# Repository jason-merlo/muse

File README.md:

# Muse
A Spark Core based music visualizer using the MSEGEQ7 spectrum analyzer IC

Bill of materials for v1.2 located at: https://docs.google.com/spreadsheets/d/1B2xJy5_H-dvUnllyMT6rd3qgGW_fhY_ttB6ZkNy4PM8/

A full writeup for this project will hopefully come sometime in the near future.

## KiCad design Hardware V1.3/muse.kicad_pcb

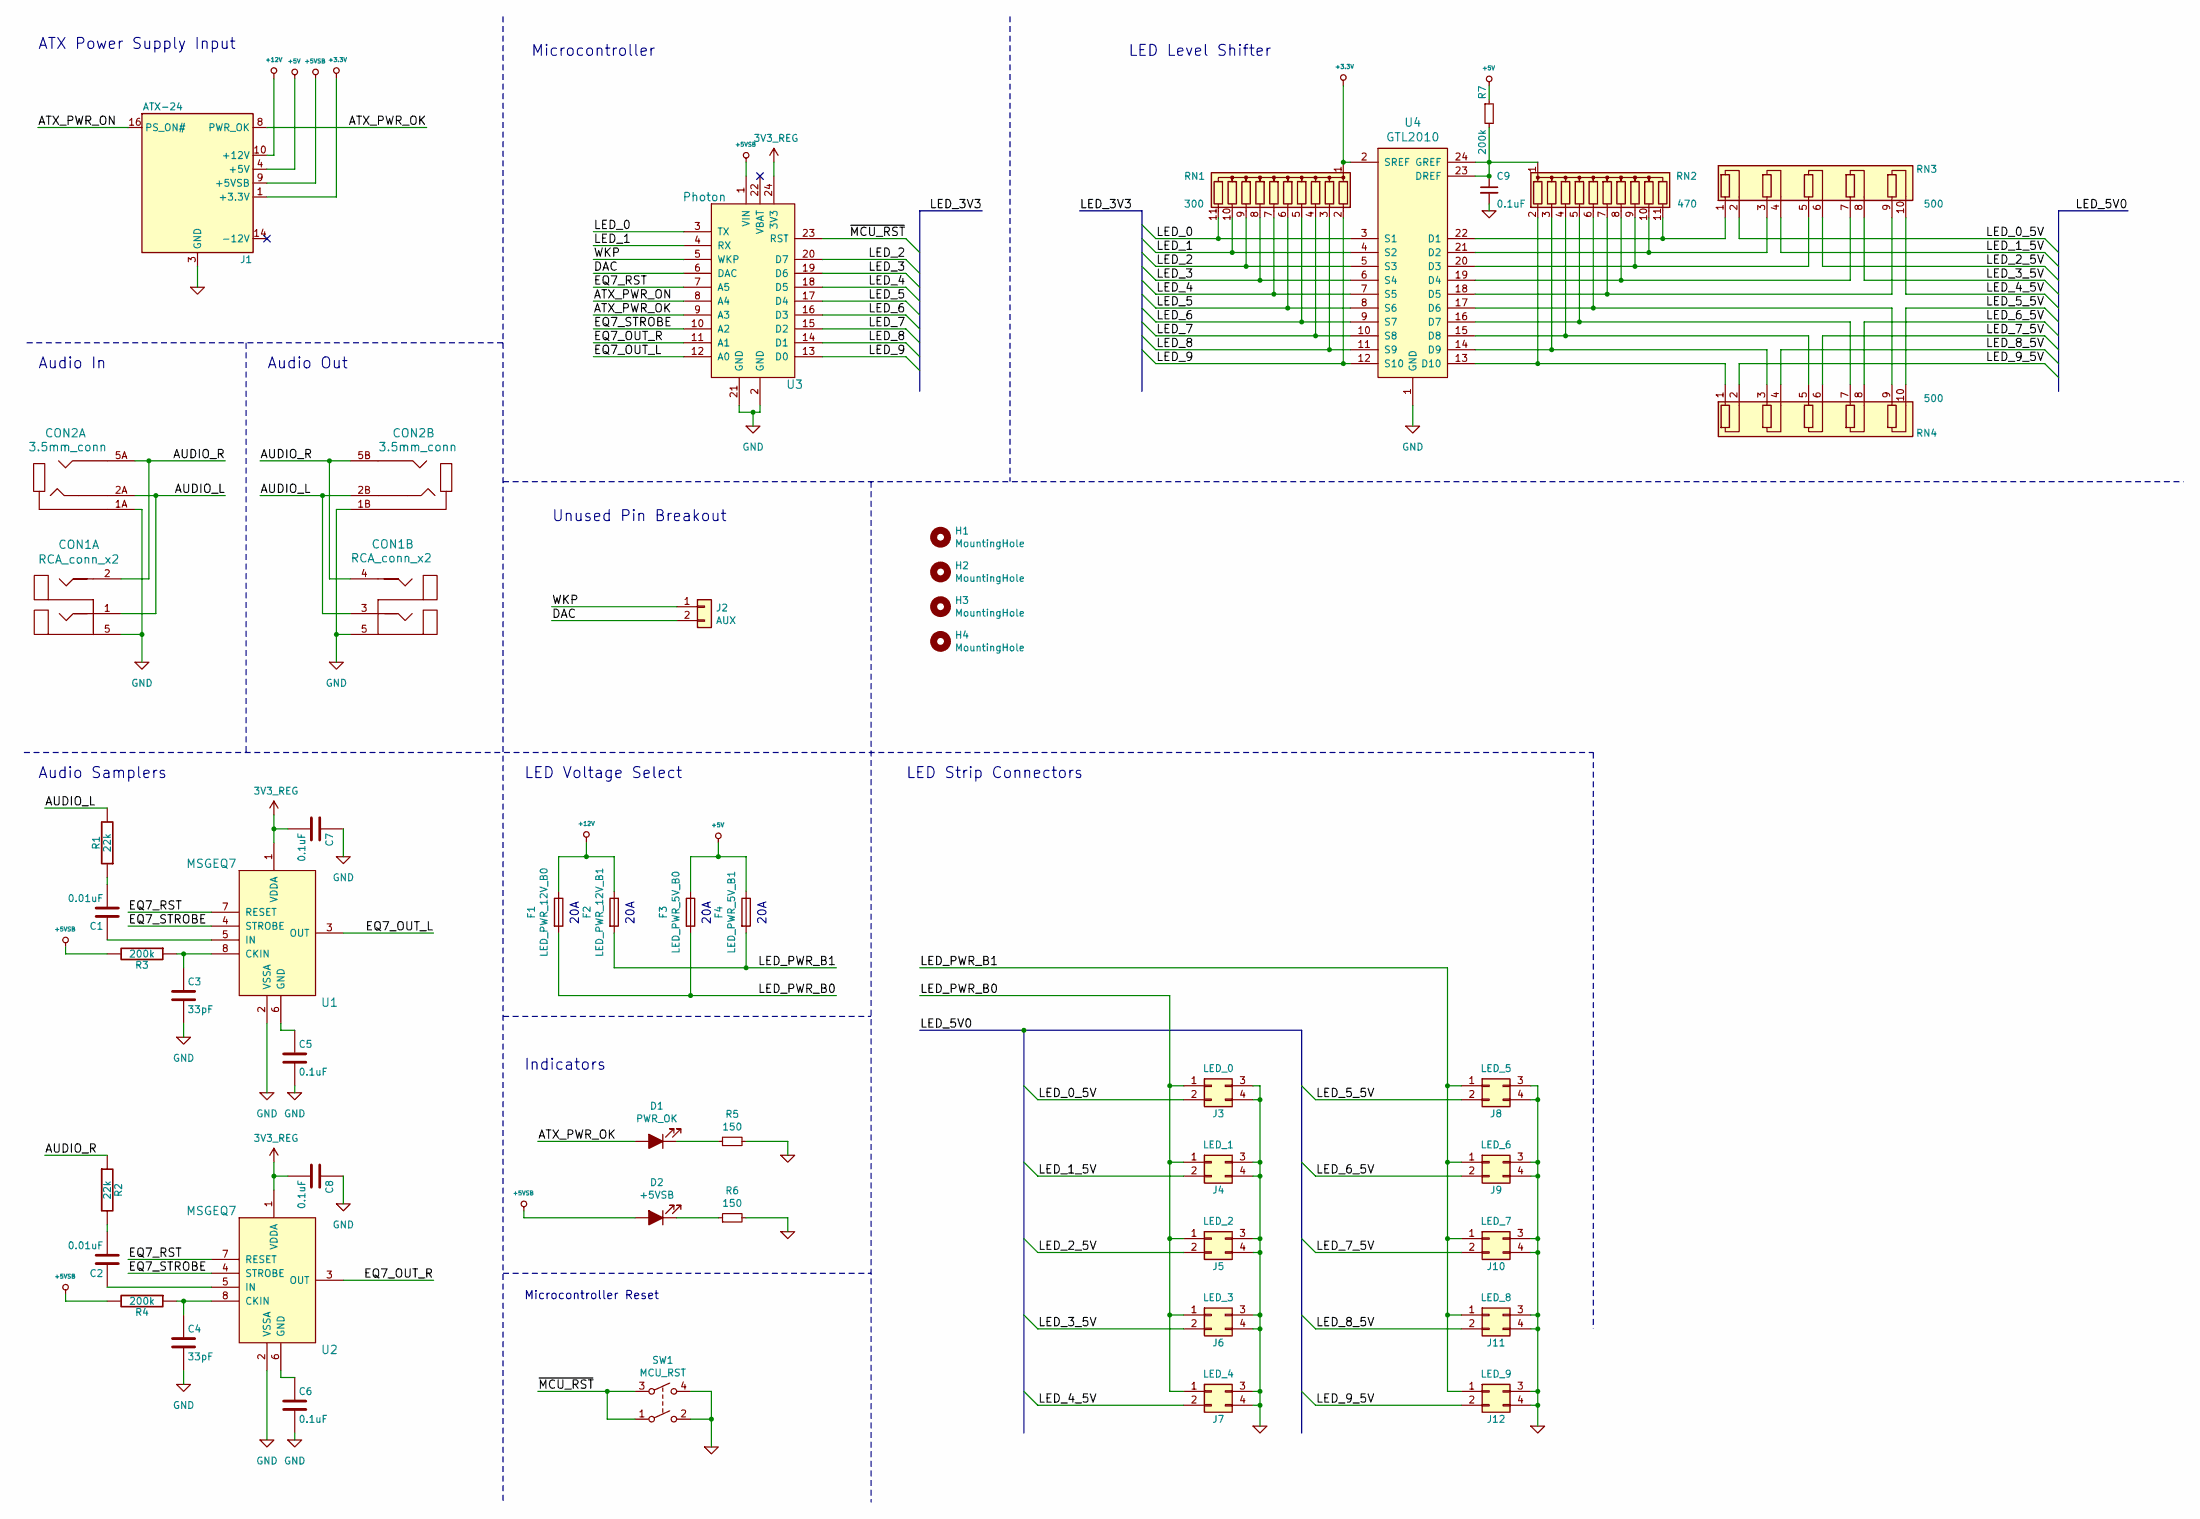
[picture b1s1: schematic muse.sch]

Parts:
C1, C2: 0.01uF; C_Rect_L4.6mm_W3.0mm_P2.50mm_MKS02_FKP02
C3, C4: 33pF; C_Rect_L4.6mm_W3.0mm_P2.50mm_MKS02_FKP02
C5, C6, C7, C8, C9: 0.1uF; C_Rect_L4.6mm_W3.0mm_P2.50mm_MKS02_FKP02
CON1: RCA_conn_x2; PJRAS2X2S01X
CON2: 3.5mm_conn; STX423535N
D1: PWR_OK; LED_D3.0mm
D2: +5VSB; LED_D3.0mm
F1: LED_PWR_12V_B0; Fuseholder_Blade_Mini_Keystone_3568
F2: LED_PWR_12V_B1; Fuseholder_Blade_Mini_Keystone_3568
F3: LED_PWR_5V_B0; Fuseholder_Blade_Mini_Keystone_3568
F4: LED_PWR_5V_B1; Fuseholder_Blade_Mini_Keystone_3568
H1, H2, H3, H4: MountingHole; MountingHole_3.2mm_M3
J1: ATX-24; Molex_Mini-Fit_Jr_5569-24A1_2x12_P4.20mm_Horizontal
J2: AUX; PinHeader_1x02_P2.54mm_Vertical
J3: LED_0; Molex_Mini-Fit_Jr_5569-04A1_2x02_P4.20mm_Horizontal
J4: LED_1; Molex_Mini-Fit_Jr_5569-04A1_2x02_P4.20mm_Horizontal
J5: LED_2; Molex_Mini-Fit_Jr_5569-04A1_2x02_P4.20mm_Horizontal
J6: LED_3; Molex_Mini-Fit_Jr_5569-04A1_2x02_P4.20mm_Horizontal
J7: LED_4; Molex_Mini-Fit_Jr_5569-04A1_2x02_P4.20mm_Horizontal
J8: LED_5; Molex_Mini-Fit_Jr_5569-04A1_2x02_P4.20mm_Horizontal
J9: LED_6; Molex_Mini-Fit_Jr_5569-04A1_2x02_P4.20mm_Horizontal
J10: LED_7; Molex_Mini-Fit_Jr_5569-04A1_2x02_P4.20mm_Horizontal
J11: LED_8; Molex_Mini-Fit_Jr_5569-04A1_2x02_P4.20mm_Horizontal
J12: LED_9; Molex_Mini-Fit_Jr_5569-04A1_2x02_P4.20mm_Horizontal
R1, R2: 22k; R_Axial_DIN0207_L6.3mm_D2.5mm_P10.16mm_Horizontal
R3, R4, R7: 200k; R_Axial_DIN0207_L6.3mm_D2.5mm_P10.16mm_Horizontal
R5, R6: 150; R_Axial_DIN0207_L6.3mm_D2.5mm_P10.16mm_Horizontal
RN1: 300; R_Array_SIP11
RN2: 470; R_Array_SIP11
RN3, RN4: 500; R_Array_SIP10
SW1: MCU_RST; SW_TH_Tactile_Omron_B3F-10xx
U1, U2: MSGEQ7; DIP-8_W7.62mm_LongPads
U3: Photon; photon_tht
U4: GTL2010; TSSOP-24_4.4x7.8mm_P0.65mm

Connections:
+3.3V: J1.1 (+3.3V), J1.2 (+3.3V), J1.12 (+3.3V), J1.13 (+3.3V), RN1.1 (common), U4.2 (SREF)
+3.3V_REG: C7.2, C8.2, U1.1 (VDDA), U2.1 (VDDA), U3.24 (3V3)
+5V: F3.1, F4.1, J1.4 (+5V), J1.6 (+5V), J1.21 (+5V), J1.22 (+5V), J1.23 (+5V), R7.1
+5VSB: D2.2 (A), J1.9 (+5VSB), R3.2, R4.2, U3.1 (VIN)
+12V: F1.1, F2.1, J1.10 (+12V), J1.11 (+12V)
/ATX_PWR_OK: D1.2 (A), J1.8 (PWR_OK), U3.9 (A3)
/ATX_PWR_ON: J1.16 (PS_ON#), U3.8 (A4)
/AUDIO_L: CON1.1, CON1.3, CON2.2A, CON2.2B, R1.2
/AUDIO_R: CON1.2, CON1.4, CON2.5A, CON2.5B, R2.1
/DAC: J2.2, U3.6 (DAC)
/EQ7_OUT_L: U1.3 (OUT), U3.12 (A0)
/EQ7_OUT_R: U2.3 (OUT), U3.11 (A1)
/EQ7_RST: U1.7 (RESET), U2.7 (RESET), U3.7 (A5)
/EQ7_STROBE: U1.4 (STROBE), U2.4 (STROBE), U3.10 (A2)
/LED_0: RN1.11 (R10), U3.3 (TX), U4.3 (S1)
/LED_0_5V: J3.2, RN3.2 (R1.2)
/LED_1: RN1.10 (R9), U3.4 (RX), U4.4 (S2)
/LED_1_5V: J4.2, RN3.4 (R2.2)
/LED_2: RN1.9 (R8), U3.20 (D7), U4.5 (S3)
/LED_2_5V: J5.2, RN3.6 (R3.2)
/LED_3: RN1.8 (R7), U3.19 (D6), U4.6 (S4)
/LED_3_5V: J6.2, RN3.8 (R4.2)
/LED_4: RN1.7 (R6), U3.18 (D5), U4.7 (S5)
/LED_4_5V: J7.2, RN3.10 (R5.2)
/LED_5: RN1.6 (R5), U3.17 (D4), U4.8 (S6)
/LED_5_5V: J8.2, RN4.10 (R5.2)
/LED_6: RN1.5 (R4), U3.16 (D3), U4.9 (S7)
/LED_6_5V: J9.2, RN4.8 (R4.2)
/LED_7: RN1.4 (R3), U3.15 (D2), U4.10 (S8)
/LED_7_5V: J10.2, RN4.6 (R3.2)
/LED_8: RN1.3 (R2), U3.14 (D1), U4.11 (S9)
/LED_8_5V: J11.2, RN4.4 (R2.2)
/LED_9: RN1.2 (R1), U3.13 (D0), U4.12 (S10)
/LED_9_5V: J12.2, RN4.2 (R1.2)
/LED_PWR_B0: F1.2, F3.2, J3.1, J4.1, J5.1, J6.1, J7.1
/LED_PWR_B1: F2.2, F4.2, J8.1, J9.1, J10.1, J11.1, J12.1
/WKP: J2.1, U3.5 (WKP)
/~MCU_RST: SW1.1, SW1.3, U3.23 (RST)
unnamed: C1.1, U1.5 (IN)
unnamed: C1.2, R1.1
unnamed: C2.1, U2.5 (IN)
unnamed: C2.2, R2.2
unnamed: C3.1, R3.1, U1.8 (CKIN)
unnamed: C4.1, R4.1, U2.8 (CKIN)
unnamed: C5.1, U1.6 (GND)
unnamed: C6.1, U2.6 (GND)
unnamed: C9.1, R7.2, RN2.1 (common), U4.23 (DREF), U4.24 (GREF)
unnamed: D1.1 (K), R5.1
unnamed: D2.1 (K), R6.1
unnamed: RN2.2 (R1), RN4.1 (R1.1), U4.13 (D10)
unnamed: RN2.3 (R2), RN4.3 (R2.1), U4.14 (D9)
unnamed: RN2.4 (R3), RN4.5 (R3.1), U4.15 (D8)
unnamed: RN2.5 (R4), RN4.7 (R4.1), U4.16 (D7)
unnamed: RN2.6 (R5), RN4.9 (R5.1), U4.17 (D6)
unnamed: RN2.7 (R6), RN3.9 (R5.1), U4.18 (D5)
unnamed: RN2.8 (R7), RN3.7 (R4.1), U4.19 (D4)
unnamed: RN2.9 (R8), RN3.5 (R3.1), U4.20 (D3)
unnamed: RN2.10 (R9), RN3.3 (R2.1), U4.21 (D2)
unnamed: RN2.11 (R10), RN3.1 (R1.1), U4.22 (D1)

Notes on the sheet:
Audio Samplers
LED Level Shifter
ATX Power Supply Input
Audio Out
Audio In
Microcontroller
LED Strip Connectors
Unused Pin Breakout
20A
LED Voltage Select
Indicators
Microcontroller Reset

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
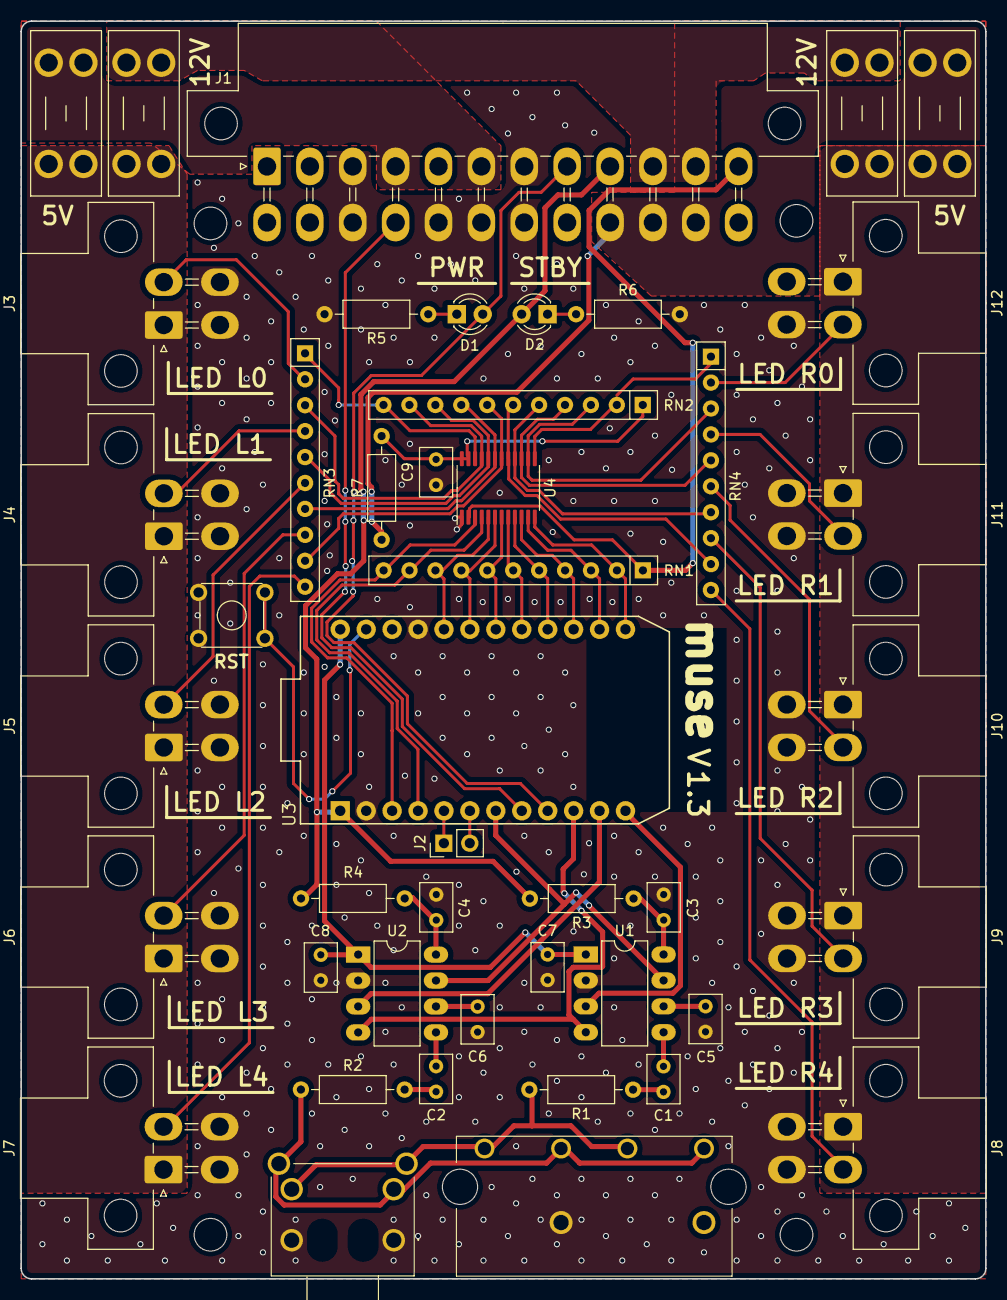
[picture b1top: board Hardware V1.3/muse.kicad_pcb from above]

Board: 2 copper layers, 94.5 x 123.2 mm, 49 parts (0 on the bottom side), 60 nets.

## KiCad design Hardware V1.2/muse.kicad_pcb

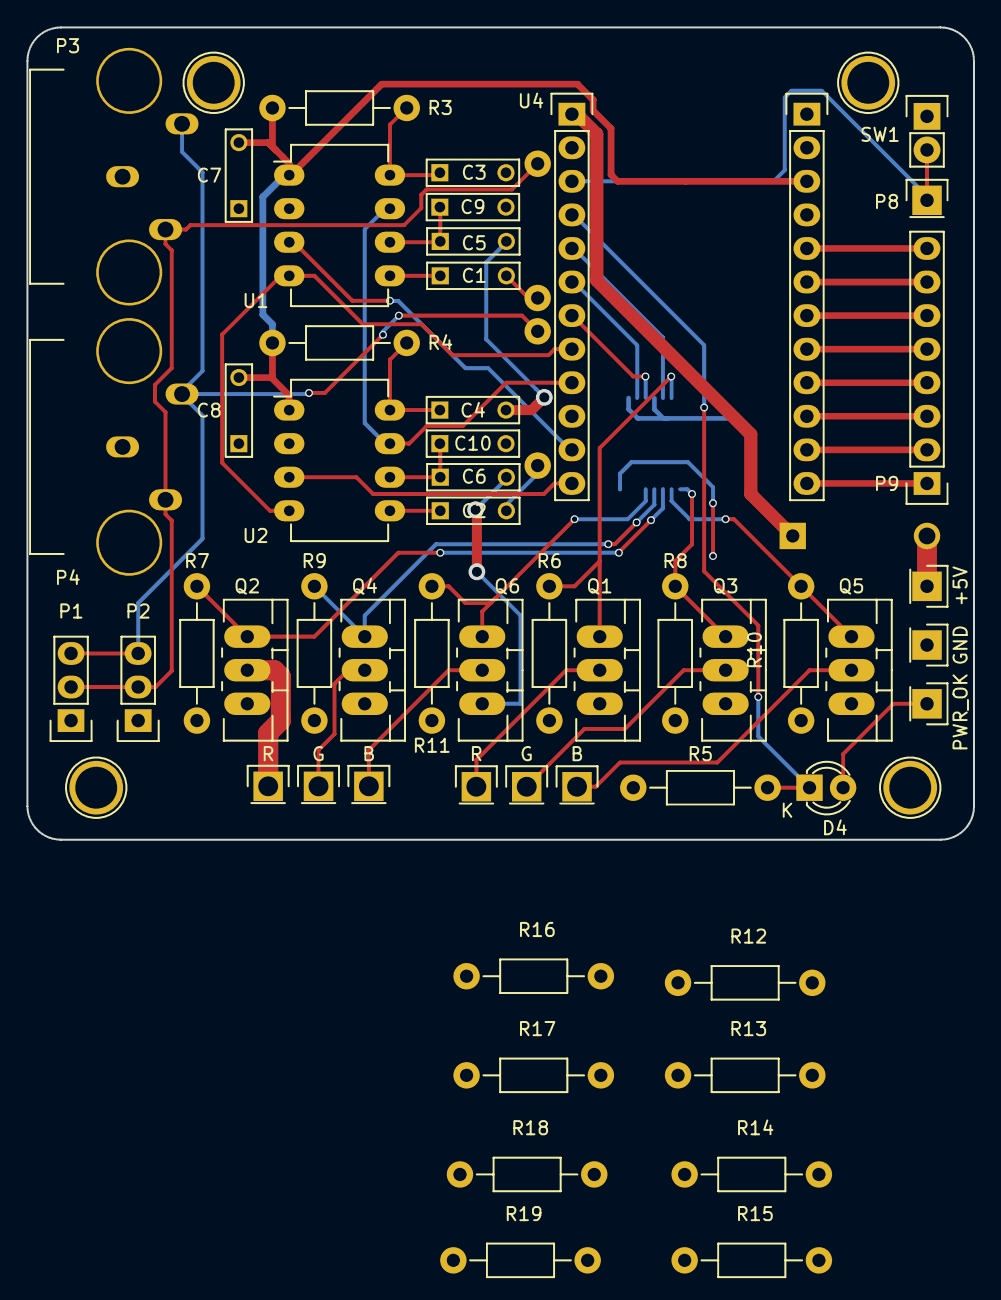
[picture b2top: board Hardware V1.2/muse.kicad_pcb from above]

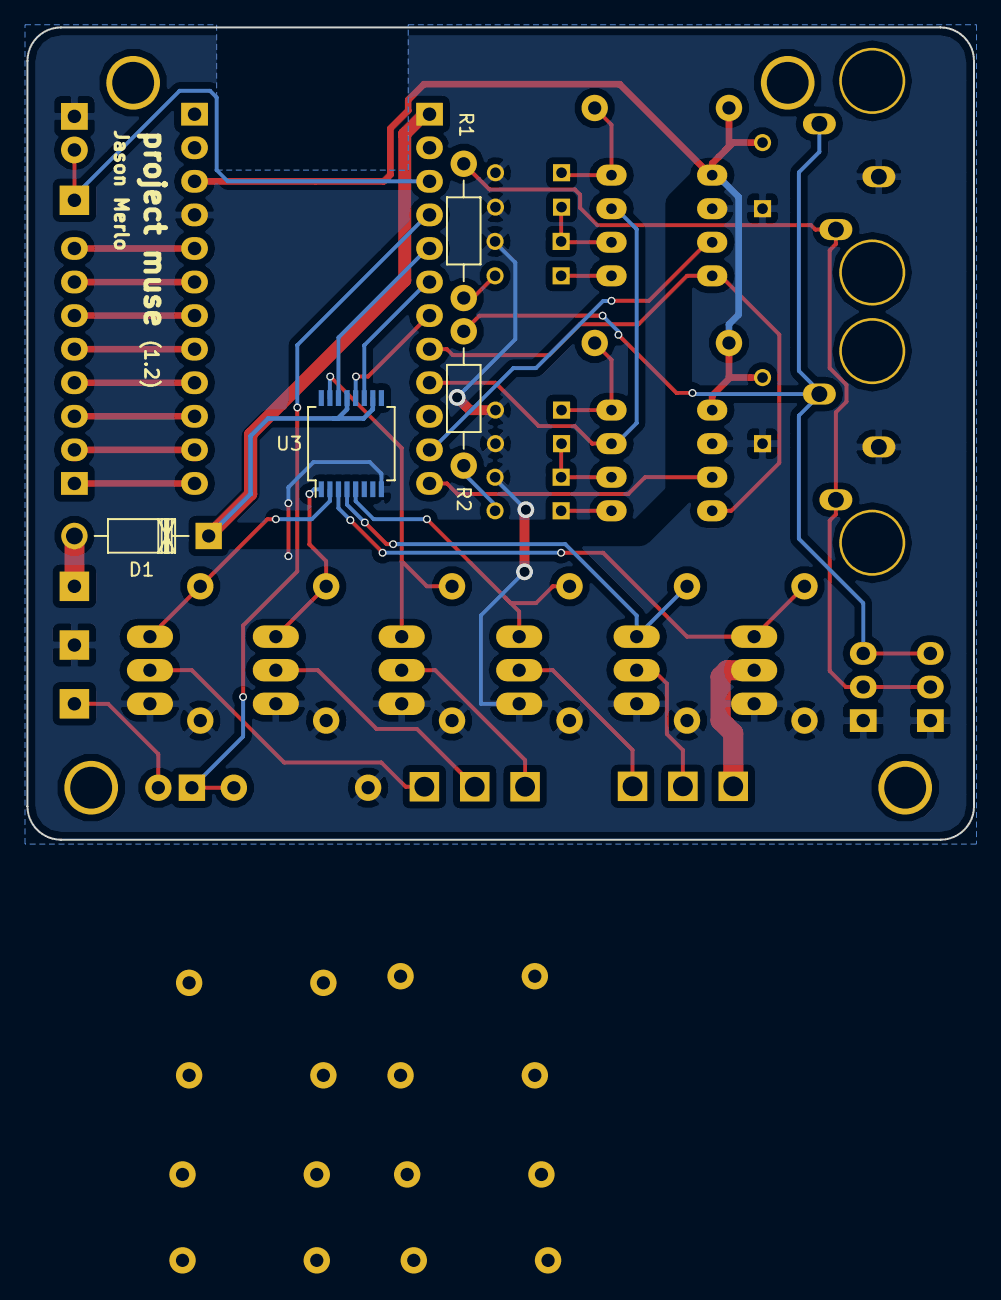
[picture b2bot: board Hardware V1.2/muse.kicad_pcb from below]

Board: 2 copper layers, 71.6 x 61.5 mm, 57 parts (4 on the bottom side), 50 nets.

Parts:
+5V: ATX_PWR; Pin_Header_Straight_1x01
B: LED_B; Pin_Header_Straight_1x01
B#2: LED_B; Pin_Header_Straight_1x01
C1, C2: 0.01uF; C_Rect_L7_W2_P5
C3, C4: 33pF; C_Rect_L7_W2_P5
C5, C6, C7, C8: 0.1uF; C_Rect_L7_W2_P5
C9, C10: 10uF; C_Rect_L7_W2_P5
D1: LED_R; Diode_DO-41_SOD81_Horizontal_RM10
D4: PWR_LED; LED-3MM
G: LED_G; Pin_Header_Straight_1x01
G#2: LED_G; Pin_Header_Straight_1x01
GND: ATX_GND; Pin_Header_Straight_1x01
P1, P2: 3.5mm_line; Pin_Header_Straight_1x03
P3, P4: RCA; Audio_RCA_Vertical
P8: ATX_PS_ON; Pin_Header_Straight_1x01
P9: LED_Signal; Pin_Header_Straight_1x08
PWR_OK: ATX_PWR_OK; Pin_Header_Straight_1x01
Q1, Q2, Q3, Q4, Q5, Q6: FQP30N06L; TO-220_Neutral123_Vertical_LargePads
R: LED_R; Pin_Header_Straight_1x01
R1, R2: 22k; Resistor_Horizontal_RM10mm
R3, R4: 200k; Resistor_Horizontal_RM10mm
R5, R12, R13, R14, R15, R16, R17, R18, R19: 470; Resistor_Horizontal_RM10mm
R6, R7, R8, R9, R10, R11: 10k; Resistor_Horizontal_RM10mm
R#2: LED_R; Pin_Header_Straight_1x01
SW1: PWR_SW; Pin_Header_Straight_1x02
U1, U2: MSGEQ7; DIP-8_W7.62mm_LongPads
U3: 74LS595; SSOP-16_5.3x6.2mm_Pitch0.65mm
U4: Spark_Core

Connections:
+3.3V: C7.2, C8.2, R3.2, R4.2, U1.1, U2.1, U4.22
+5V: U3.10, U3.13, U4.1
/ATX_PWR_OK: D4.1, U4.4
/ATX_PWR_ON: P8.1, U4.3
/Aout_L: U1.3, U4.11
/Aout_R: U2.3, U4.12
/LED_0: R12.2, U4.13
/LED_0_B: Q5.1, R10.2, U3.2
/LED_0_G: Q3.1, R8.2, U3.1
/LED_0_R: Q1.1, R6.2, U3.15
/LED_1: R13.2, U4.14
/LED_1_B: Q6.1, R11.2, U3.5
/LED_1_G: Q4.1, R9.2, U3.4
/LED_1_R: Q2.1, R7.2, U3.3
/LED_2: R14.2, U4.15
/LED_3: R15.2, U4.16
/LED_4: R16.2, U4.17
/LED_5: R17.2, U4.18
/LED_6: R18.2, U4.19
/LED_7: R19.2, U4.20
/RGB_CLK: U3.11, U4.6
/RGB_DAT: U3.14, U4.5
/RGB_LAT: U3.12, U4.7
/RST: U1.7, U2.7, U4.9
/STROBE: U1.4, U2.4, U4.8
/audio_l: P1.2, P2.2, P3.2, P4.2, R1.2
/audio_r: P1.3, P2.3, P3.3, P4.3, R2.1
GND: C3.2, C4.2, C5.2, C6.2, C7.1, C8.1, C9.2, C10.2, GND.1, P1.1, P2.1, P3.1, P4.1, Q1.3, Q2.3, Q3.3, Q4.3, Q5.3, Q6.3, R5.1, R6.1, R7.1, R8.1, R9.1, R10.1, R11.1, SW1.1, U1.2, U2.2, U3.8, U4.2, U4.21
unnamed: C1.1, U1.5
unnamed: C1.2, R1.1
unnamed: C2.1, U2.5
unnamed: C2.2, R2.2
unnamed: C3.1, R3.1, U1.8
unnamed: C4.1, R4.1, U2.8
unnamed: C5.1, C9.1, U1.6
unnamed: C6.1, C10.1, U2.6
unnamed: D1.1, Q1.2
unnamed: Q5.2, R#2.1
unnamed: D4.2, R5.2
unnamed: G.1, Q2.2
unnamed: G#2.1, Q4.2
unnamed: B.1, Q6.2
unnamed: P9.1, R12.1
unnamed: P9.2, R13.1
unnamed: P9.3, R14.1
unnamed: P9.4, R15.1
unnamed: P9.5, R16.1
unnamed: P9.6, R17.1
unnamed: P9.7, R18.1
unnamed: P9.8, R19.1

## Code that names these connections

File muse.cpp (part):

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#if EXTENDED_LAYOUT
// Digital Outputs
static const char rst     = RX;
static const char strobe  = DAC;

// Analog Inputs (0-4096)
static const char audio_r = A2;
static const char audio_l = A3;

#if RGB_LIGHTS
static char rgb_pins_l[3] = {A5, TX, WKP};
static char rgb_pins_r[3] = {D0, D1, A4};
#endif
#else
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// Digital Outputs
static const char ps_on   = -1;
static const char rst     = A3;
static const char strobe  = A4;

// Digital Inputs
static const char pwr_sw  = D4;

// Analog Inputs (0-4096)
static const char audio_r = A0;
static const char audio_l = A1;
#endif

// Declare memory for audio bin structure
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    // Enables frequency analyzer
    #if ENABLE_MSGEQ7
    pinMode(rst, OUTPUT);
    pinMode(strobe, OUTPUT);
    pinMode(audio_l, INPUT);
    pinMode(audio_r, INPUT);
    init_eq();
    last_sample_millis = 0;
    #endif
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
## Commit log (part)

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2015-09-15 :tada: Added .gitattributes
2015-09-15 Initial commit
    Adding sample_freq function
2015-09-19 Added Neopixel library, PSU functionality pins, started testing audio
2015-09-20 Added logic for leds from audio binning
    Testing only
2015-09-20 Working software prototype, starting PCB modeling
2015-09-20 Added Power Switch (v1 complete)
2015-09-22 Updated power distibution
    Removed onboard power routing to allow for high current wire to be
    added directly to terminal block.
2015-09-22 Created custom footprints and added to PCB
    Setting up PCB
2015-09-22 Preliminary PCB Layout in progress
2015-09-22 Preliminary board layout complete
    TODO: Route circuitry
2015-09-23 Completed muse v1.0 board
2015-09-26 Updated test source code, final PCB layout
2015-09-27 updated beta visualizer code
2015-10-28 Created matrix class, started final testing code
2015-11-13 Basic bars visualizer with right channel workaround
2015-11-17 Added lots of function documentation, added per-feature #define enables
2015-11-17 Added a .gitignore to ignore binaries
2015-11-17 Fixed decay, added decay factor
2015-11-17 Added title blocks to files
2015-11-17 Removed un-needed delay in main loop
2015-11-18 Added fading per-pixel in and out on bar visualizer
    Additionally, removed wheel function
2015-12-19 Started V2
2015-12-19 Finished updates schematic, removed gerber files
2015-12-21 Added more ground paths to v2
2015-12-21 Gerbers generated and sent to Oshpark
2015-12-21 Changed versioning scheme. Fixed problems and reuploaded to oshpark
2016-01-11 Implemented fill matrix, added constants
2016-01-11 Fixes for PCB revision 1.1
    PSU power is controlled by the core. PSU is on whenever the core is on
    by default.
2016-01-12 Bars_middle visualizer and more constants
    visualizer_bars_middle is similar to visualizer_bars but it uses both
    MSGEQ7s. It draw the right channel filling up from the middle in the
    bars and the left channel filling down.
    Also added more constants for better control of what visualizers run.
2016-01-12 Rename constants for enabling displays/features
    RUN_ #defines now decide which visualizer to draw to the bars.
    ENABLE_ #defines now decide what features are enabled (MSGEQs/PSU
    control etc)
2016-01-13 Added a sleep/psu auto off function. Still buggy
    Weird bug slows down everything once the music stops
2016-01-13 Fixed up screensaver/auto shutoff
    Using Time.now() as it is way more accurate than millis().
    Millis() looses track of time when interrupts are turned off for a long
    period of time as they are in the neopixel library. Time.now seems much
    more accurate.
2016-01-13 Clear_matrix and show_all before psu change
    Prevents flashing on startup/shutdown
2016-01-13 Tweak color values for bouncing lines
2016-01-14 Created V1.2 Project, Completed marked "issues" in schematic
    PCB still needs to be updated
2016-01-14 Fixed merge conflict
2016-01-14 Began work on pulse visualizer; not yet complete
2016-01-14 Cleaning up code, screensaver & power in progress
2016-01-14 Added switch for visualizers, cleaned up bouncing lines
2016-01-15 Fixed channels and updated visualizer setups for more customization
2016-01-17 Added strobe mode, still buggy
2016-01-19 Fixed ENABLE_AUTO_SHUTDOWN flag, indenting
2016-01-19 Currently serving small static webpage
2016-01-24 Created rainbow visualizer. Added call to init_eq. Tweak sleep values.
2016-02-06 Added 8th bar average and sharper cut off for color rather than a fade out.
2016-02-13 Removed 7 bar setups, Added Plasma visualizer (indev)
2016-02-13 Added speed to plasma visualizer
2016-02-13 Adjusted color scheme and speed of plasma
2016-02-13 Refactored bin naming
2016-02-27 First janky iteration of beat detection
2016-03-04 added moar trade secrets and cleanup
2016-03-04 whatever
2016-03-20 Better beat detection.
2016-03-23 Fixed random turn-ons from noise
2016-04-05 Added beat detection colors to many visualizers. Just commented out their previous colorings. Reordered bins going into the Bars visualizer
2016-04-05 Browsers can now connect to the webserver.
    Made this work by calling tcp_client.stop() after serving the webpage. Probably not what we want for the final implementation but it gets the html sent to your browser for now. Need to learn more abo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
2016-04-06 Updated footprints, added gnd fill keep out
2016-04-07 Updated power paths and RF keepouts
    Currently editing transistor GND path sizes
2016-04-08 Add 1ms delay to main loop
    Corrects issues with flashing new code from the cloud taking many attemps to succeed.
2016-04-08 Clean up 1 line of spacing
2016-04-08 Alphabetize and renumber visualizer constants
2016-04-08 Initial commit of Beat_Detection class.
    Will hold beat detection data and functions to clean up the Bar_Matrix a bit.
2016-04-08 Finished setting up beat detection class. Need to test/integrate into bar_matrix.
2016-04-08 Disabled webserver
2016-04-08 Fixed indentation on function headers
2016-04-09 Group and reorder/alphabetize functions
    All the functions in here were mixed together kinda randomly. Made a few functions private since they didn't need to be called from outside this class. Alphabetize functions within their subgroups (p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
2016-04-09 Move visualizer selection logic to bar_matrix
    It was in Muse.cpp, now it is in the tick function in Bar_Matrix
2016-04-09 A function header
2016-04-10 Add back in call to sample_freq. Accidentally removed during merging.
2016-04-12 Webserver works when it is the only thing enabled.
    Need to debug working with other stuff enabled.
2016-04-21 Switch to Jason\'s multicolored bars
2016-04-21 Disable webserver for now
2016-04-21 num_beats now returns the number of beats that have been detected
2016-04-21 Forgat a mod 3
2016-05-03 Initial Webduino 'port'. Currently serving up a Hello World page via HTTP.
    Will clean up new classes and create better defineguards in next few commits.
2016-05-03 Cleaning up and commenting
2016-05-03 Remove some unneeded includes and comments
2016-05-03 Remove and rearrage includes
2016-05-03 Serving webpage with slider for visualizer control. Change the red slider to change visualizers
2016-05-04 Webserver with working radio buttons to select visualizer.
    Connect to the server's IP and click a radio button to choose a visualizer.
2016-05-05 More options added to web control panel.
    Also added some code to use mDNS, that's not working + commented out.
2016-05-05 Fixed minor bug in handling other bar displays
2016-05-13 Modified Rainbow visualizer and remove unneeded server code.
2016-05-14 Great tweaks to rainbow visualizer
2016-05-16 Begin adding webpage controlled power.
    Still need to implement checking function in server.cpp... Need to change callback signitures for the webserver first.
2016-05-16 Working callbacks/power on and off buttons. Disabled AUTO_SHUTDOWN of PSU.
    Callbacks from the WebServer library now include a pointer to a given object (usually server.cpp instance). There is also a power button on the webpage now.
    Disabled Auto Shutdown of PSU in order to use the webpage on/off buttons. Best solution I have for now. It could probably be fixed to work with both in the future fairly easily.
2016-05-16 Cleaned up and added some comments.
    Removed old/unused variables/functions. Added function headers. Removed unused webpages from webpage.h
2016-05-20 Added interval timer to web server ticks to reduce light latency
2016-05-20 Trying my damnedest to fix stupid :)
2016-05-20 Added ambient light selector to control panel
2016-05-21 Use jQuery to POST now instead of forms
2016-05-21 Change switches that validate input.
2016-05-21 Added MDNS support. Connect to http://muse.local/
    Using library from https://github.com/mrhornsby/spark-core-mdns
2016-05-25 Added lib folder, moved stuff into it.
    The MDNS server and webserver files got put into lib/mdns and lib/webserver.
    Also added lib_info.txt to each lib folder to at least give a link to their github repos.
2016-05-25 Removed webpage.html as it was unused
2016-05-25 Add update interval for display.
    Current visualizer, bin sampling, and beat detection now run every DISPLAY_UPDATE_INTERVAL millis instead of each time the main loop is run. Helps a bit with server/mdns responsiveness. Also increase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
    Added misc trackers to display on cloud variables.
2016-06-15 Initial PiServer commit
2016-06-15 Removed all webserver things from pi_server class
2016-06-15 Working communication between Pi and Photon
    No longer attempting SPI. Using one wire for data, one as a 'data received' by the Photon and one as a 'data ready' from the Pi. The Pi puts data on the data line, toggles the value of the data ready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
2016-06-16 Improve data transfer speeds.
    Each tick the data transfer routine will run for 50 microseconds. Each bit takes approx 5 micros to send so this should allow for a transfer rate of 1 Byte/tick to the Photon.
2016-06-16 Skeleton for parsing packets from Pi.
    PiServer now calls get_byte() every tick. If a full byte was recieved then it will process it. If not, it will wait until the next tick and attempt to finish receiving a byte.
2016-06-16 Some comments
2016-06-16 More comments to PiServer.cpp
2016-07-23 Update pi server to handle power on/off and all visualizers
2016-07-31 Separate beat detection from bar matrix
    This change allows for beat detection even when not drawing any new frames. The beat detection instance is stored in muse and is passed by reference to the bar matrix instance. Muse's tick function i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
2016-08-01 Update beat detection moving average lengths and add a periodic reset to pi server communication
2016-08-02 Beat detection improvements
2016-08-02 Added new data and added a header with data info at top
2016-08-02 Edited data header
2016-08-10 Correct BIN_MAX from 4096 to 4095
2016-08-10 Add beat detection for every bin.
    Old beat detection is still avaliable, called bpm detection now. Per bin beat detection is also avaliable.
2016-08-11 Added classic visualizer and several helper methods to bar_matrix.
    Bar matrix can now fill bar with a color and decay to a color. Classic visualizer added based on my original, pre-muse, visualizer.
2016-08-11 Added communications timeout between pi and photon to avoid loss of communication.
2016-08-12 Cleanup, adjust include guards, powered_on_tick method to control sampling/frame updates
    Variables/rountines should now be properly disabled based on the ENABLE_X values in muse.h. Created a powered_on_tick() method to run sampling/beat detection/frame updates. Updated the main loop to m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
2016-08-12 Move commonly changed settings to settings.h
    Per user/per hardware instance settings will no longer be committed. Should keep us from messing with each other's settings.
2016-08-12 Add settings.h to gitignore
2016-08-12 All systems enabled defines default to 0
2016-08-12 Add define guard to some psu control in powered_on_tick
2016-09-25 New bouncing lines visualizer. Change bars middle to use the color table.
    Bouncing lines overhaul, individual colors and speeds for all of the lines.
    Bars middle now changes to a new color from the color table on a beat.
2016-09-25 Adding snake lines visualizer
2016-09-25 One snake works hella good
2016-09-25 Bugfix on snake
2016-09-25 Snake struct created, add as many snakes as you want
2016-10-15 Start pong visualizer
2016-10-15 Pong visualizer progress
2016-10-15 Fix some define guards
2016-11-04 Add bass_middle visualizer
2016-11-06 Convert from wired communication to UDP communication
2016-11-07 Working UDP send
2016-11-12 Added extended mode, some RGBLED stuff
2017-01-11 Add bass slide visualizer and fix IP address
2017-02-04 Spicy code update sliding into your DMs
2017-03-05 Fix pong paddle bouncing
2017-04-15 Speed up decay on bars visualizer, reorder bars, print IP address
2017-04-15 Un delete files from master. See steven branch for work
2017-04-15 Remove webpage html
2017-04-23 Fix beat detection initialization in visualizer.h, update classic visualizer
2017-04-23 Pass reference to audio bins in constructors instead of in tick()
2017-04-23 Added bass_slide, rainbow, plasma in new format
2017-04-23 Bugfixes and change visualizer.h COLOR_TABLE2 to COLOR_TABLE
2017-04-23 Implemented all visualizers in new format. Removed wheel because it didnt do anything.
    All tested and working on steven's setup :)
2017-05-18 Added mesh visualizer, work in progress
2017-09-10 Updated colors
2017-09-10 Fixed broken MDNS and added proper define guards for web server
    Fixed bar layout for new house
2021-03-27 Added rev 1.3
